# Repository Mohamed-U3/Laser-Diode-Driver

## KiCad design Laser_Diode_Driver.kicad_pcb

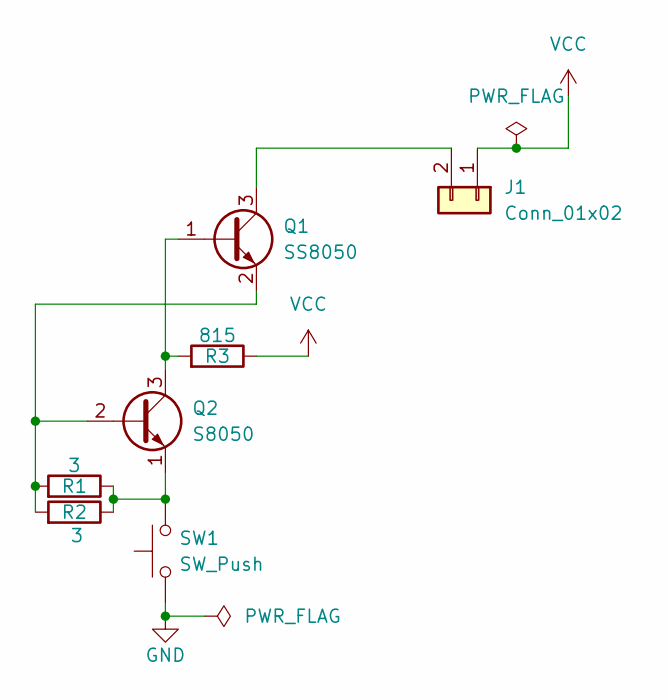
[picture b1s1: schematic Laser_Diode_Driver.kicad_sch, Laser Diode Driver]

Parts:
J1: Conn_01x02; JST_XA_B02B-XASK-1_1x02_P2.50mm_Vertical
Q1: SS8050; SOT-23
Q2: S8050; SOT-23
R1, R2: 3; R_0402_1005Metric
R3: 815; R_0402_1005Metric
SW1: SW_Push; SW_Push_1P1T_NO_E-Switch_TL3301NxxxxxG

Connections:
GND: SW1.1
unnamed: J1.2, Q1.3 (C)
unnamed: Q1.1 (B), Q2.3 (C), R3.1
unnamed: Q1.2 (E), Q2.2 (B), R1.1, R2.1
unnamed: Q2.1 (E), R1.2, R2.2, SW1.2
VCC: J1.1, R3.2

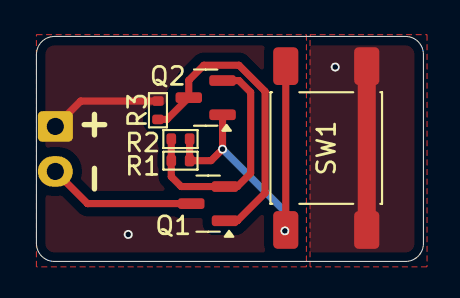
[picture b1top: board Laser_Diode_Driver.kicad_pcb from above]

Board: 2 copper layers, 21.5 x 12.5 mm, 7 parts (0 on the bottom side), 5 nets.

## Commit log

2025-08-27 fix: small modification on the silkscreen for information.
